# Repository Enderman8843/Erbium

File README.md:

# Erbium

It is Hi-Speed USB HUB with USB2514B_B Chip and 24mhz crystal , With Support of USB C aswell as USB A

## How To Use ?
JUST PlUG IT INTO YOUR COMPUTER VIA THE INPUT

## Why did I built it 
I built this project because I wanted learn more about usb hubs and their working , WHile this hub also helps me to work with my RPI 2 zero , which dosent have many usb ports and hence allowing me to connect multiple peripeheral devices to it 

# PCB Layout

| PCB Layout | Schematic / Wiring |
|------------|-------------------|
|  |  |

# PCB Render

| Front | Rear |
|-------|------|
|  |  |

# Case 

---

# BOM

| Item | Description | Quantity | Unit Price ($) | Total Price ($) | URL |
|------|-------------|----------|----------------|-----------------|-----|
| PCBA | Custom PCB Manufacturing (JLCPCB) | 1 | 31.00 | 31.00 | https://jlcpcb.com |
| Case | 3D Printed Case (Will be Printed Myself | 1 | 0.00 | 0.00 | https://hackclub.com |
| USB Connector | USB Type-A Vertical Through-Hole Connector (Adam Tech USB-A-S-VT) | 1 | 2.00 | 2.00 | https://www.digikey.in/en/products/detail/adam-tech/USB-A-S-VT/9832290 |
| **TOTAL** |  |  |  | **33.00** |  |

# JLCPCB and Shipping

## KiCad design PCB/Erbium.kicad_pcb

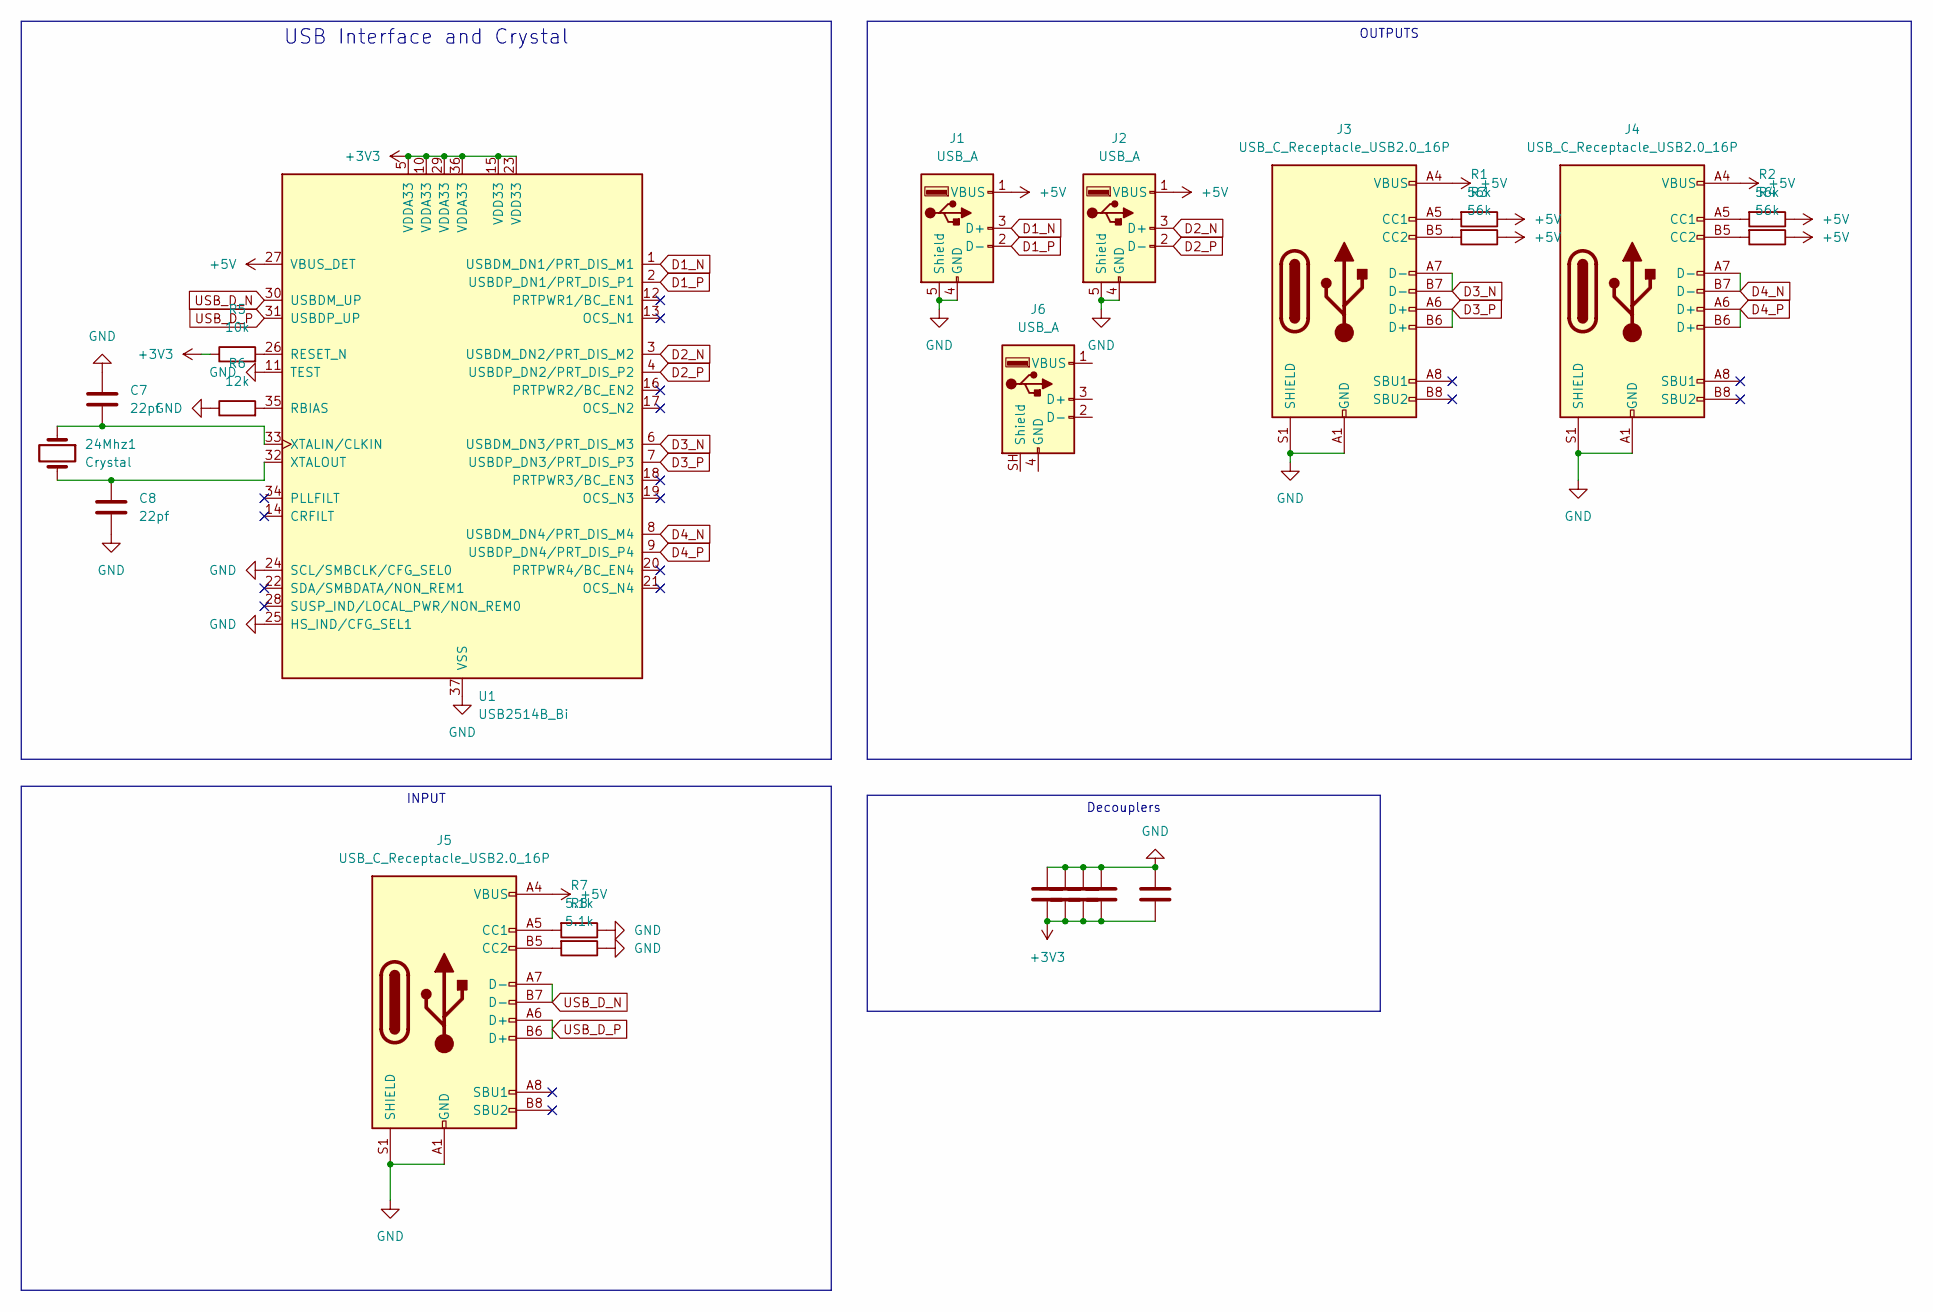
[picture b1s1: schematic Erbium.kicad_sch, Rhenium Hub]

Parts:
24Mhz1: Crystal; Crystal_SMD_3225-4Pin_3.2x2.5mm
C5, C9, C10, C11, C12: 0.1µF; C_0603_1608Metric
C7, C8: 22pf; C_0603_1608Metric
J1, J2: USB_A; USB_A_Molex_105057_Vertical
J3, J4, J5: USB_C_Receptacle_USB2.0_16P; USB_C_Receptacle_G-Switch_GT-USB-7010ASV
J6: USB_A
R1, R2, R3, R4: 56k; C_0603_1608Metric
R5: 10k; C_0603_1608Metric
R6: 12k; C_0603_1608Metric
R7, R8: 5.1k; C_0603_1608Metric
U1: USB2514B_Bi; QFN-36-1EP_6x6mm_P0.5mm_EP3.7x3.7mm

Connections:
+3V3: C5.2, C9.2, C10.2, C11.2, C12.2, R5.1, U1.5 (VDDA33), U1.10 (VDDA33), U1.15 (VDD33), U1.23 (VDD33), U1.29 (VDDA33), U1.36 (VDDA33)
+5V: J1.1 (VBUS), J2.1 (VBUS), J3.A4 (VBUS), J3.A9 (VBUS), J3.B4 (VBUS), J3.B9 (VBUS), J4.A4 (VBUS), J4.A9 (VBUS), J4.B4 (VBUS), J4.B9 (VBUS), J5.A4 (VBUS), J5.A9 (VBUS), J5.B4 (VBUS), J5.B9 (VBUS), R1.1, R2.1, R3.1, R4.1, U1.27 (VBUS_DET)
D1_N: J1.3 (D+), U1.1 (USBDM_DN1/PRT_DIS_M1)
D1_P: J1.2 (D-), U1.2 (USBDP_DN1/PRT_DIS_P1)
D2_N: J2.3 (D+), U1.3 (USBDM_DN2/PRT_DIS_M2)
D2_P: J2.2 (D-), U1.4 (USBDP_DN2/PRT_DIS_P2)
D3_N: J3.A7 (D-), J3.B7 (D-), U1.6 (USBDM_DN3/PRT_DIS_M3)
D3_P: J3.A6 (D+), J3.B6 (D+), U1.7 (USBDP_DN3/PRT_DIS_P3)
D4_N: J4.A7 (D-), J4.B7 (D-), U1.8 (USBDM_DN4/PRT_DIS_M4)
D4_P: J4.A6 (D+), J4.B6 (D+), U1.9 (USBDP_DN4/PRT_DIS_P4)
GND: C5.1, C7.1, C8.2, C9.1, C10.1, C11.1, C12.1, J1.4 (GND), J1.5 (Shield), J2.4 (GND), J2.5 (Shield), J3.A1 (GND), J3.A12 (GND), J3.B1 (GND), J3.B12 (GND), J3.S1 (SHIELD), J4.A1 (GND), J4.A12 (GND), J4.B1 (GND), J4.B12 (GND), J4.S1 (SHIELD), J5.A1 (GND), J5.A12 (GND), J5.B1 (GND), J5.B12 (GND), J5.S1 (SHIELD), R6.1, R7.1, R8.1, U1.11 (TEST), U1.24 (SCL/SMBCLK/CFG_SEL0), U1.25 (HS_IND/CFG_SEL1), U1.37 (VSS)
unnamed: J3.A5 (CC1), R1.2
unnamed: J3.B5 (CC2), R3.2
unnamed: J4.A5 (CC1), R2.2
unnamed: J4.B5 (CC2), R4.2
unnamed: J5.A5 (CC1), R7.2
unnamed: J5.B5 (CC2), R8.2
unnamed: R6.2, U1.35 (RBIAS)
unnamed: R5.2, U1.26 (RESET_N)
unnamed: 24Mhz1.1, C7.2, U1.33 (XTALIN/CLKIN)
unnamed: 24Mhz1.2, C8.1, U1.32 (XTALOUT)
USB_D_N: J5.A7 (D-), J5.B7 (D-), U1.30 (USBDM_UP)
USB_D_P: J5.A6 (D+), J5.B6 (D+), U1.31 (USBDP_UP)

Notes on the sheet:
INPUT
OUTPUTS
Decouplers
USB Interface and Crystal

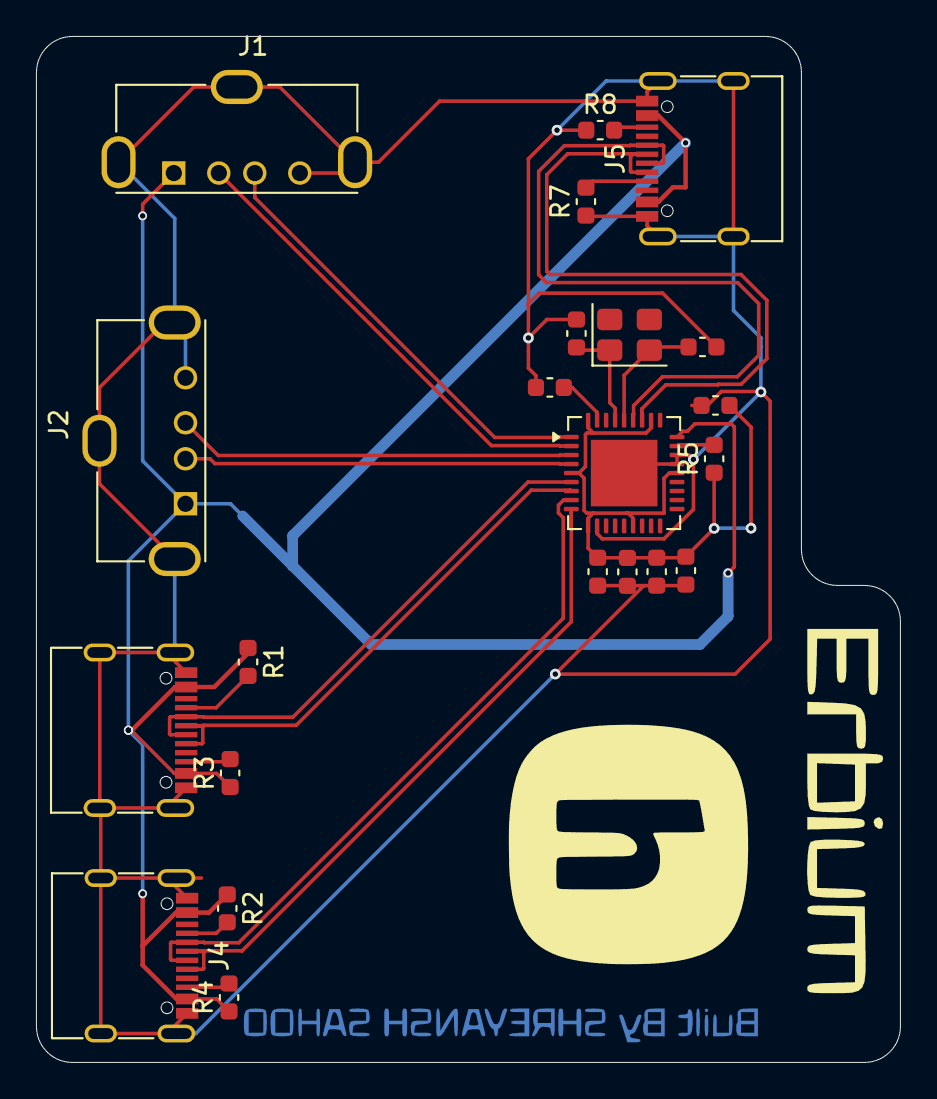
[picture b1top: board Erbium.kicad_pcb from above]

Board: 2 copper layers, 48.0 x 57.0 mm, 22 parts (0 on the bottom side), 23 nets.

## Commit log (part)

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2026-05-17 Updated the pcb
2026-06-10 hihi
2026-06-14 Modify case description and recalculate total price
    Updated the case description and adjusted total price.
